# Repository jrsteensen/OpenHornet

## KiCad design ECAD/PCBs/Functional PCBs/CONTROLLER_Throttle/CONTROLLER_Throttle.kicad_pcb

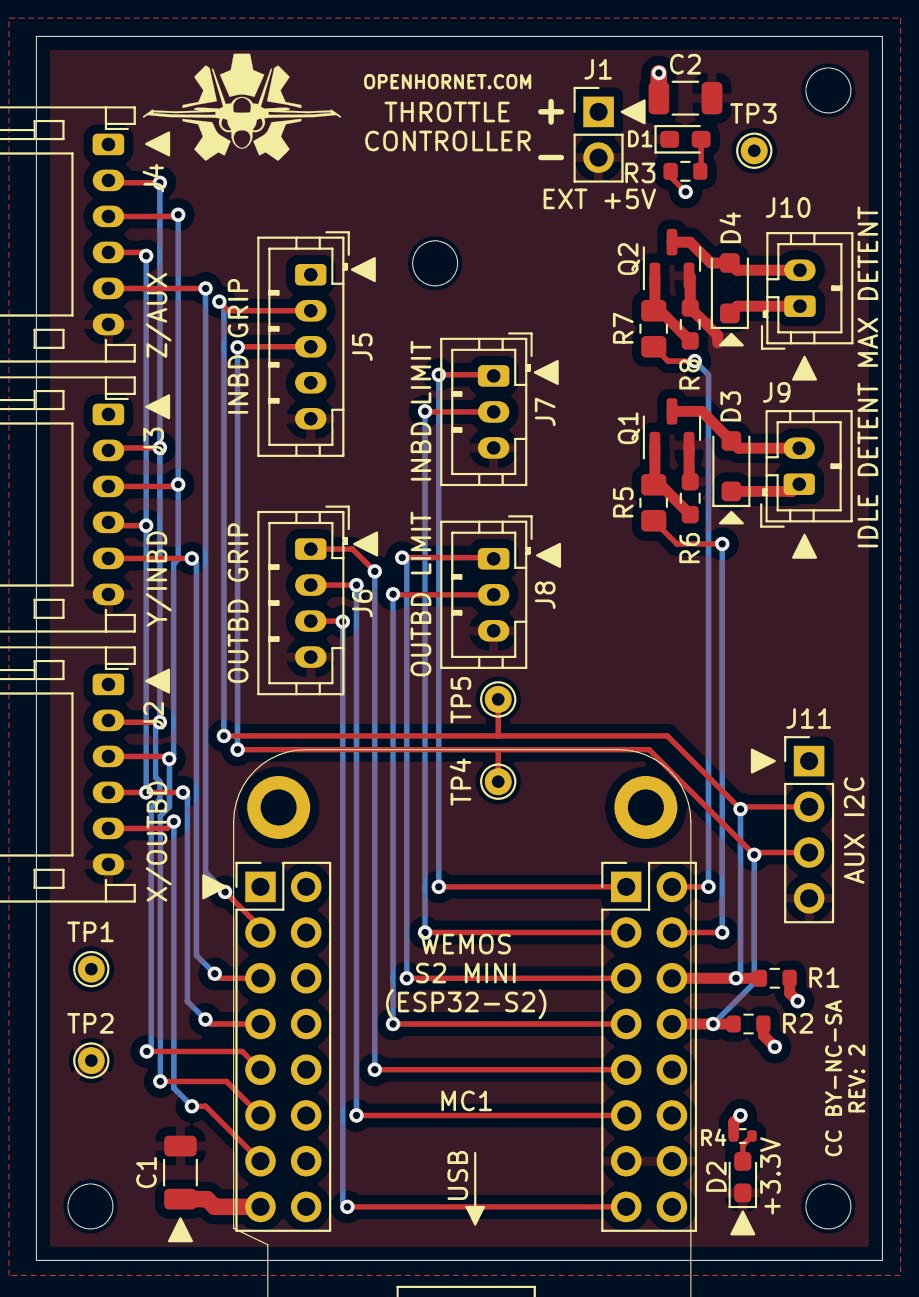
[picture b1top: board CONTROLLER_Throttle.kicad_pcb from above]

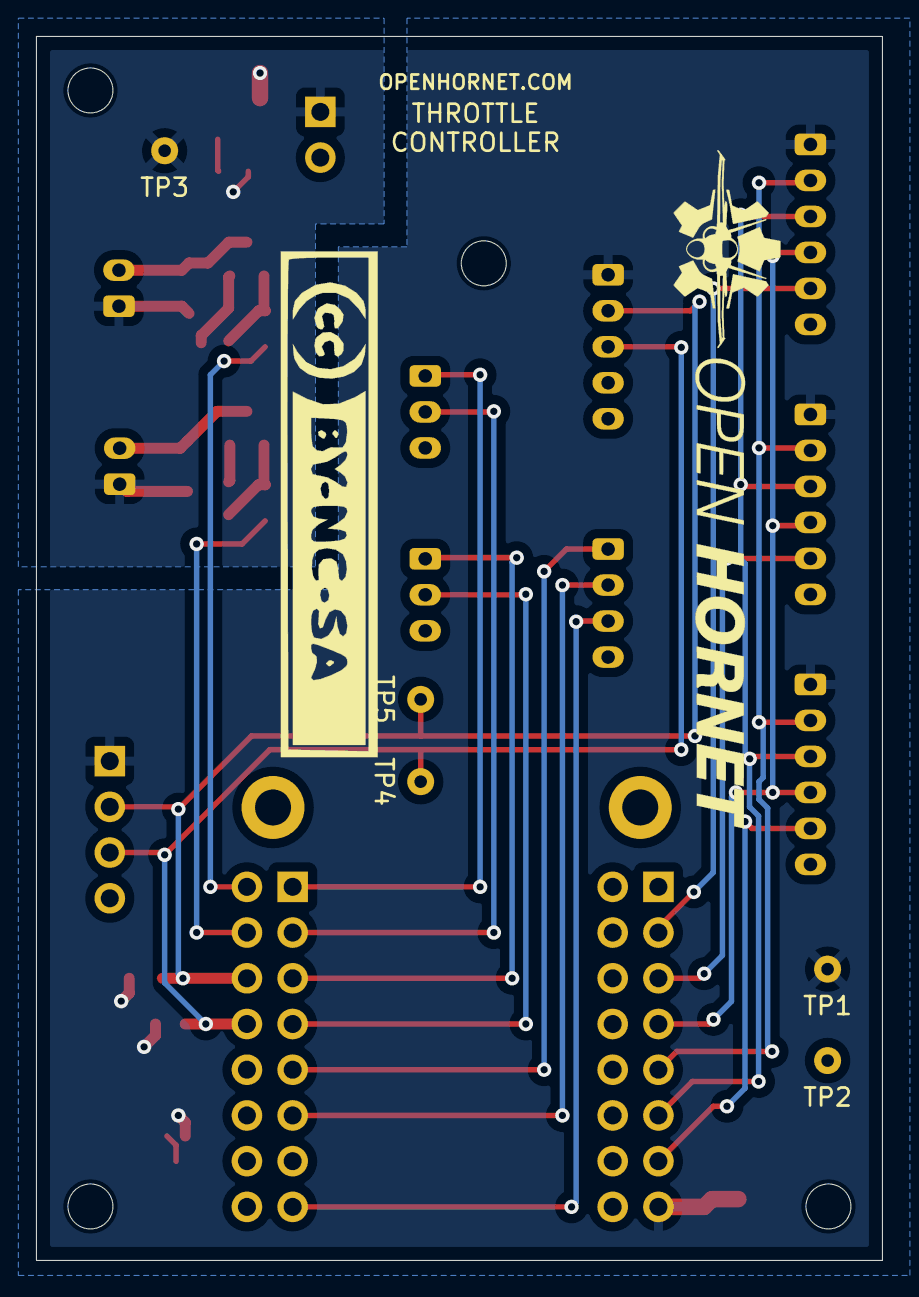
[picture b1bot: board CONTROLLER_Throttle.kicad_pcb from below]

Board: 2 copper layers, 47.0 x 68.0 mm, 40 parts (2 on the bottom side), 26 nets.

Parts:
C1, C2: 10uF; C_1206_3216Metric
D1: +5V_PWR; LED_0603_1608Metric_Pad1.05x0.95mm_HandSolder
D2: +3.3V_PWR; LED_0603_1608Metric_Pad1.05x0.95mm_HandSolder
D3, D4: 1N4002W; D_SOD-123F
J1: EXT +5V; PinHeader_1x02_P2.54mm_Vertical
J2: X/OUTBD; JST_PH_S6B-PH-K_1x06_P2.00mm_Horizontal
J3: Y/INBD; JST_PH_S6B-PH-K_1x06_P2.00mm_Horizontal
J4: Z/AUX; JST_PH_S6B-PH-K_1x06_P2.00mm_Horizontal
J5: INBD GRIP; JST_PH_B5B-PH-K_1x05_P2.00mm_Vertical
J6: OUTBD GRIP; JST_PH_B4B-PH-K_1x04_P2.00mm_Vertical
J7: INBD LIMIT; JST_PH_B3B-PH-K_1x03_P2.00mm_Vertical
J8: OUTBD LIMIT; JST_PH_B3B-PH-K_1x03_P2.00mm_Vertical
J9: IDLE DETENT; JST_PH_B2B-PH-K_1x02_P2.00mm_Vertical
J10: MAX DETENT; JST_PH_B2B-PH-K_1x02_P2.00mm_Vertical
J11: AUX I2C; PinHeader_1x04_P2.54mm_Vertical
LOGO1: OpenHornetLogoSmall; OH_LOGO_37.7mm_5.9mm
LOGO2: OpenHornetLogoSmall; CC-BY-NC-SA-Small
LOGO3: OpenHornetLogoSmall; OH_LOGO_ONLY_11x6mm
MC1: S2_MINI
MH1, MH2, MH3, MH4: MH; MountingHole_2.5mm
Q1, Q2: IRLML6402TRPBF; SOT-23
R1, R2: 4.7k; R_0603_1608Metric
R3: 120; R_0603_1608Metric
R4: 33; R_0402_1005Metric
R5, R7: 1K; R_0805_2012Metric_Pad1.20x1.40mm_HandSolder
R6, R8: 10K; R_0603_1608Metric_Pad0.98x0.95mm_HandSolder
TP1: 3v3; TestPoint_THTPad_D1.5mm_Drill0.7mm
TP2: GND; TestPoint_THTPad_D1.5mm_Drill0.7mm
TP3: 5VA; TestPoint_THTPad_D1.5mm_Drill0.7mm
TP4: SDA; TestPoint_THTPad_D1.5mm_Drill0.7mm
TP5: SCL; TestPoint_THTPad_D1.5mm_Drill0.7mm

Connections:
+3.3V: C1.1, J2.1, J3.1, J4.1, J5.1, J11.1, MC1.8 (+3.3V), R1.1, R2.2, R4.1, TP1.1
+5VA: C2.1, D3.1 (K), D4.1 (K), J1.1, J9.1, J10.1, R3.1, TP3.1
ATC ENGAGE: J6.3, MC1.24 (IO15)
CSx: J2.5, MC1.7 (IO12)
CSy: J3.5, MC1.3 (IO5)
CSz: J4.5, MC1.2 (IO3)
EXT LTS: J6.1, MC1.21 (IO21)
GND: C1.2, C2.2, D1.1 (K), D2.1 (K), J1.2, J2.6, J3.6, J4.6, J5.5, J6.4, J7.3, J8.3, J11.4, MC1.23 (GND1), MC1.31 (GND2), Q1.2 (S), Q2.2 (S), R6.2, R8.2, TP2.1
IDLE SOL SIG: MC1.26 (IO37), R5.1
INBD IDLE LIMIT: J7.2, MC1.18 (IO38)
INBD MAX LIMIT: J7.1, MC1.17 (IO40)
MAX SOL SIG: MC1.25 (IO39), R7.1
MISO: J2.2, J3.2, J4.2, MC1.5 (IO9/MISO)
MOSI: J2.3, J3.3, J4.3, MC1.6 (IO11/MOSI)
unnamed: D1.2 (A), R3.2
unnamed: D2.2 (A), R4.2
unnamed: D3.2 (A), J9.2, Q1.3 (D)
unnamed: D4.2 (A), J10.2, Q2.3 (D)
unnamed: Q1.1 (G), R5.2, R6.1
unnamed: Q2.1 (G), R7.2, R8.1
OUTBD IDLE LIMIT: J8.2, MC1.20 (IO34)
OUTBD MAX LIMIT: J8.1, MC1.19 (IO36)
RAID/FLIR: J6.2, MC1.22 (IO17/DAC1)
SCK: J2.4, J3.4, J4.4, MC1.4 (IO7/SCK)
SCL: J5.2, J11.2, MC1.27 (IO35/SCL), R1.2, TP5.1
SDA: J5.3, J11.3, MC1.28 (IO33/SDA), R2.1, TP4.1

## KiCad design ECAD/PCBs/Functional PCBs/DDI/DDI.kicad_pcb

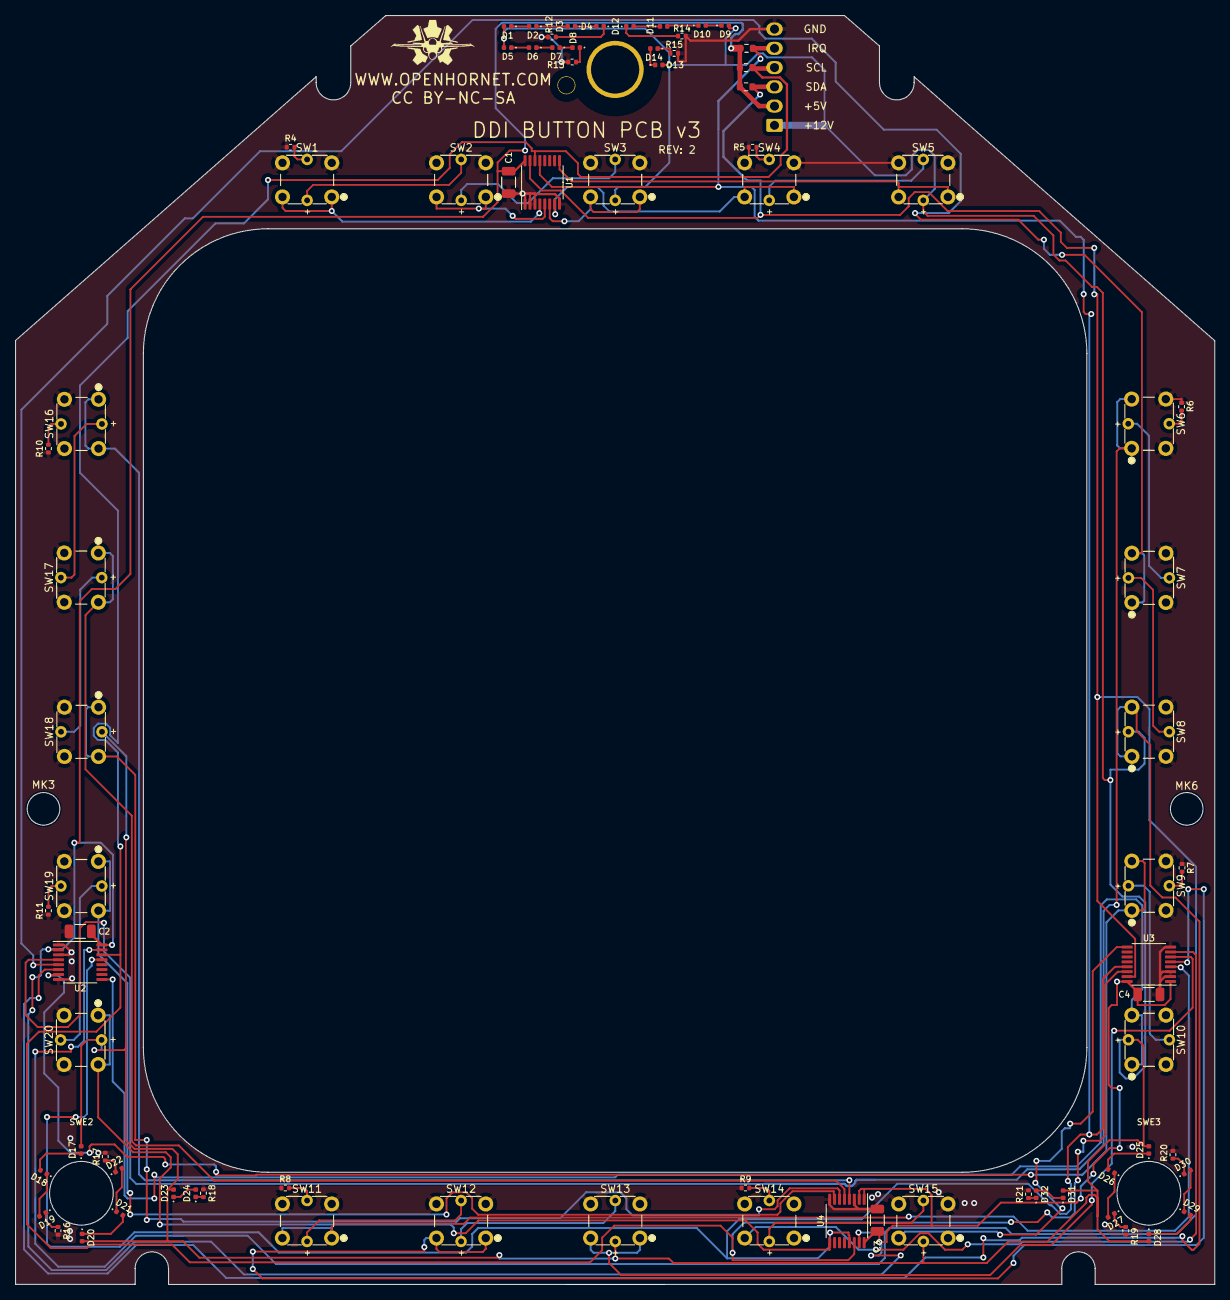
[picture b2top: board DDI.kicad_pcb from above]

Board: 2 copper layers, 158.2 x 167.4 mm, 85 parts (1 on the bottom side), 56 nets.

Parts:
C1, C2, C3, C4: 47uF; C_1206_3216Metric
D1, D2, D3, D4, D5, D6, D7, D8, D9, D10, D11, D12, D13, D14, D17, D18, D19, D20, D21, D22, D23, D24, D25, D26, D27, D28, D29, D30, D31, D32: LED; LED_0402_1005Metric
J1: Conn_01x06; Molex_KK-254_AE-6410-06A_1x06_P2.54mm_Vertical
MK3, MK6: MH; MountingHole_4.3mm_M4
R1, R2, R3: 10K; R_0603_1608Metric
R4, R6, R8, R10, R16, R17, R19, R20: 150; R_0402_1005Metric
R5, R7, R9, R11, R15, R18, R21: 270; R_0402_1005Metric
R12, R13, R14: 33; R_0402_1005Metric
SW1, SW2, SW3, SW4, SW5, SW6, SW7, SW8, SW9, SW10, SW11, SW12, SW13, SW14, SW15, SW16, SW17, SW18, SW19, SW20: TL1240GQ
SWE1: MRY106_RotarySW
SWE2, SWE3: MountingHole_8.4mm_M8
U1, U2, U3, U4: TCA9554PWR; TSSOP-16_4.4x5mm_P0.65mm

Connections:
+5V: C1.1, C2.1, C3.1, C4.1, J1.2, R1.1, R2.1, R3.1, U1.16, U2.2, U2.16, U3.1, U3.16, U4.1, U4.2, U4.16
/U1P0: SW1.1, U1.4
/U1P1: SW2.1, U1.5
/U1P2: SW3.1, U1.6
/U1P3: SW4.1, U1.7
/U1P4: SW5.1, U1.9
/U2P0: SW6.1, U2.4
/U2P1: SW7.1, U2.5
/U2P2: SW8.1, U2.6
/U2P3: SW9.1, U2.7
/U2P4: SW10.1, U2.9
/U3P0: SW11.1, U3.4
/U3P1: SW12.1, U3.5
/U3P2: SW13.1, U3.6
/U3P3: SW14.1, U3.7
/U3P4: SW15.1, U3.9
/U4P0: SW16.1, U4.4
/U4P1: SW17.1, U4.5
/U4P2: SW18.1, U4.6
/U4P3: SW19.1, U4.7
/U4P4: SW20.1, U4.9
GND: C1.2, C2.2, C3.2, C4.2, J1.6, R4.1, R5.1, R6.1, R7.1, R8.1, R9.1, R10.1, R11.1, R12.2, R13.2, R14.2, R15.2, R16.2, R17.2, R18.2, R19.2, R20.2, R21.2, SW1.2, SW2.2, SW3.2, SW4.2, SW5.2, SW6.2, SW7.2, SW8.2, SW9.2, SW10.2, SW11.2, SW12.2, SW13.2, SW14.2, SW15.2, SW16.2, SW17.2, SW18.2, SW19.2, SW20.2, U1.1, U1.2, U1.3, U1.8, U2.1, U2.3, U2.8, U3.2, U3.3, U3.8, U4.3, U4.8
IRQ: J1.5, R1.2, U1.13, U2.13, U3.13, U4.13
unnamed: D1.1, D2.2
unnamed: D2.1, D3.2
unnamed: D3.1, D4.2
unnamed: D4.1, R12.1
unnamed: D5.1, D6.2
unnamed: D6.1, D7.2
unnamed: D7.1, D8.2
unnamed: D8.1, R13.1
unnamed: D10.1, D11.2
unnamed: D9.1, D10.2
unnamed: D11.1, D12.2
unnamed: D12.1, R14.1
unnamed: D13.1, D14.2
unnamed: D14.1, R15.1
unnamed: D17.1, D18.2
unnamed: D18.1, D19.2
unnamed: D19.1, R16.1
unnamed: D20.1, D21.2
unnamed: D21.1, D22.2
unnamed: D22.1, R17.1
unnamed: D23.1, D24.2
unnamed: D24.1, R18.1
unnamed: D25.1, D26.2
unnamed: D26.1, D27.2
unnamed: D27.1, R19.1
unnamed: D28.1, D29.2
unnamed: D29.1, D30.2
unnamed: D30.1, R20.1
unnamed: D31.1, D32.2
unnamed: D32.1, R21.1
SCL: J1.4, R2.2, U1.14, U2.14, U3.14, U4.14
SDA: J1.3, R3.2, U1.15, U2.15, U3.15, U4.15
VCC: D1.2, D5.2, D9.2, D13.2, D17.2, D20.2, D23.2, D25.2, D28.2, D31.2, J1.1

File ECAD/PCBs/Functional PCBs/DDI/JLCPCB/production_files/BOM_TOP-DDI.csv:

Comment,Designator,Footprint,LCSC
LED,"D1,D10,D11,D12,D13,D14,D17,D18,D19,D2,D20,D21,D22,D23,D24,D25,D26,D27,D28,D29,D3,D30,D31,D32,D4,D5,D6,D7,D8,D9",LED_0402_1005Metric,C130723
150,"R10,R16,R17,R19,R20,R4,R6,R8",R_0402_1005Metric,C25082
270,"R11,R15,R18,R21,R5,R7,R9",R_0402_1005Metric,C25099
33,"R12,R13,R14",R_0402_1005Metric,C25105
10K,"R1,R2,R3",R_0603_1608Metric,C25804
TCA9554PWR,"U1,U2,U3,U4",TSSOP-16_4.4x5mm_P0.65mm,C477924
47uF,"C1,C2,C3,C4",C_1206_3216Metric,C96123
TL1240GQ_old,SW1,TL1240GQ_old,
TL1240GQ_old,SW2,TL1240GQ_old,
TL1240GQ_old,SW3,TL1240GQ_old,
TL1240GQ_old,SW4,TL1240GQ_old,
TL1240GQ_old,SW5,TL1240GQ_old,
TL1240GQ_old,SW6,TL1240GQ_old,
TL1240GQ_old,SW7,TL1240GQ_old,
TL1240GQ_old,SW8,TL1240GQ_old,
TL1240GQ_old,SW9,TL1240GQ_old,
TL1240GQ_old,SW10,TL1240GQ_old,
TL1240GQ_old,SW11,TL1240GQ_old,
TL1240GQ_old,SW12,TL1240GQ_old,
TL1240GQ_old,SW13,TL1240GQ_old,
TL1240GQ_old,SW14,TL1240GQ_old,
TL1240GQ_old,SW15,TL1240GQ_old,
TL1240GQ_old,SW16,TL1240GQ_old,
TL1240GQ_old,SW17,TL1240GQ_old,
TL1240GQ_old,SW18,TL1240GQ_old,
TL1240GQ_old,SW19,TL1240GQ_old,
TL1240GQ_old,SW20,TL1240GQ_old,

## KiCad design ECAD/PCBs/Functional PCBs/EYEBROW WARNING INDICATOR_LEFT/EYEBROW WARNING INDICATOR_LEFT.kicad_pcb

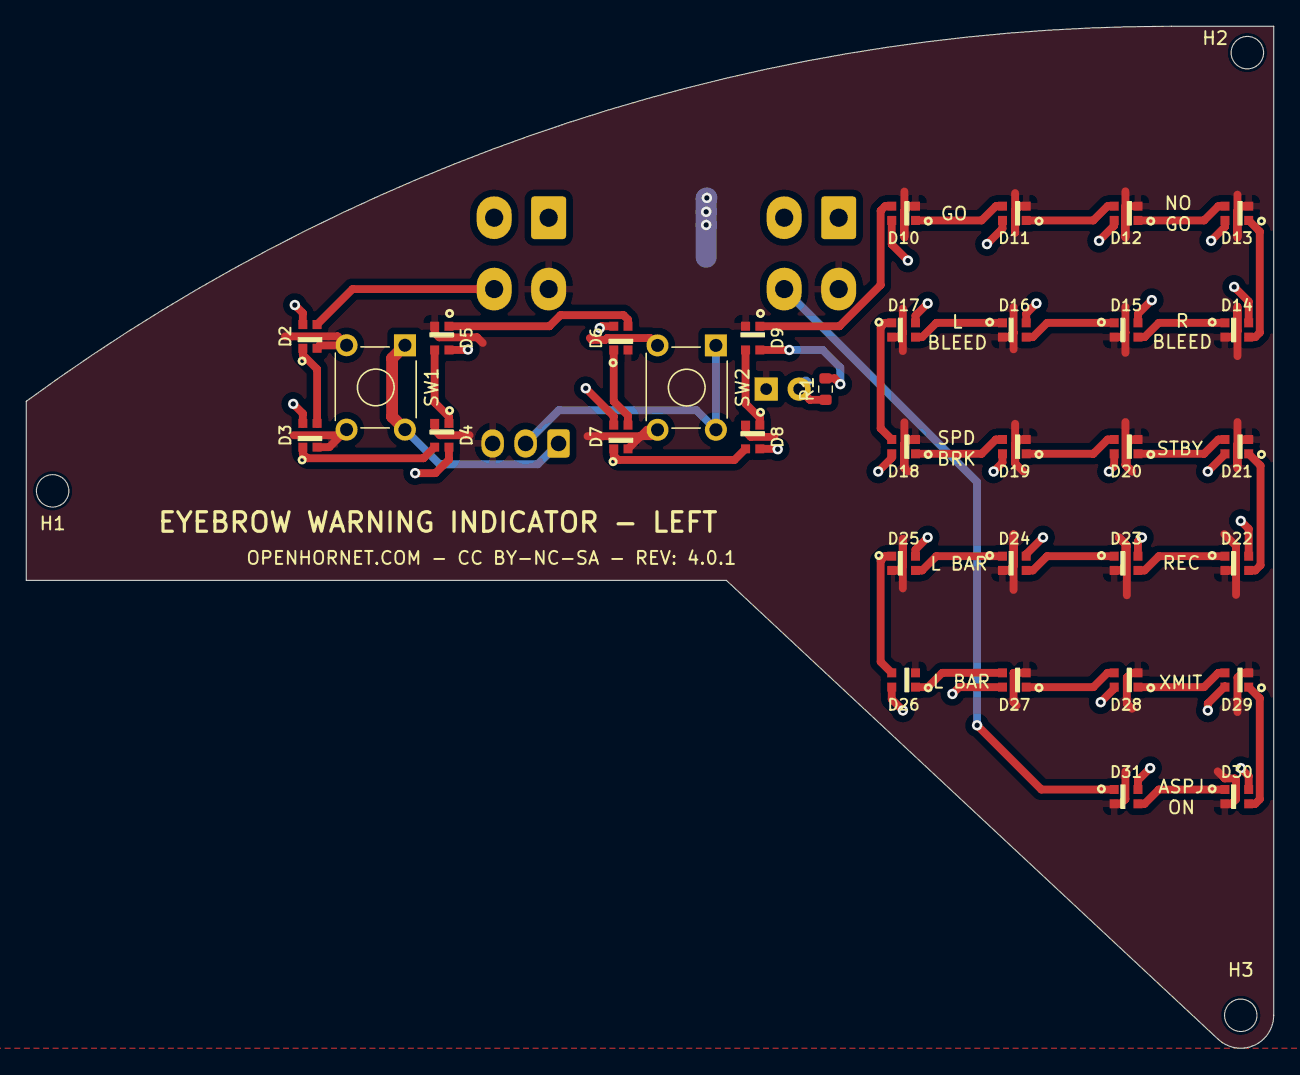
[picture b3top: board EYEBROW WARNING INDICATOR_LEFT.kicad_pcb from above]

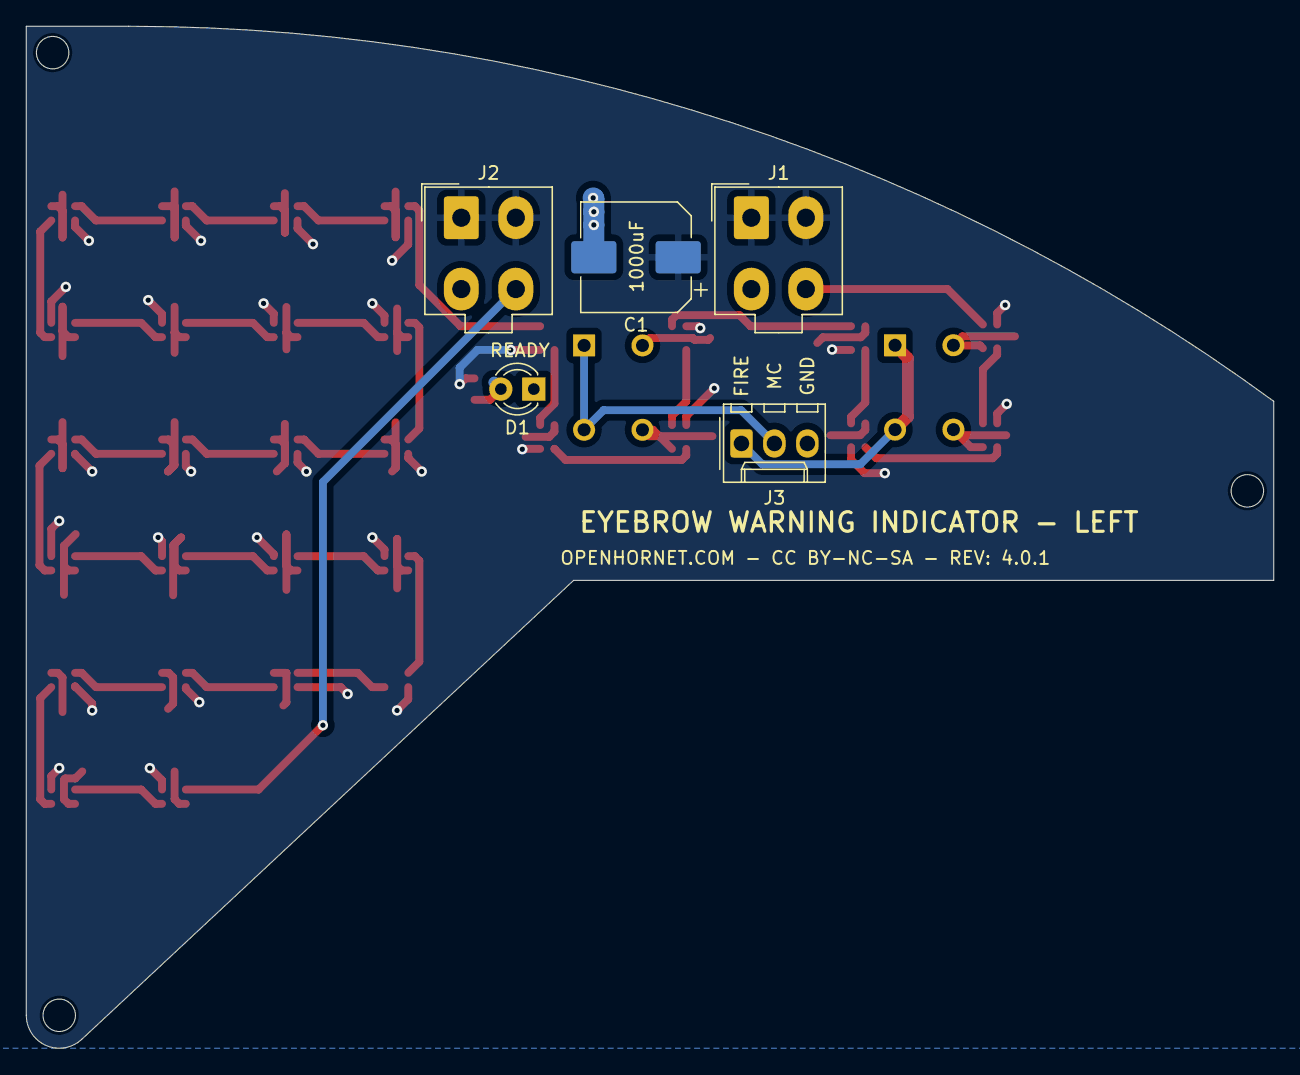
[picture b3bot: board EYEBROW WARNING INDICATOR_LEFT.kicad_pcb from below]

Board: 2 copper layers, 96.1 x 78.8 mm, 41 parts (5 on the bottom side), 36 nets.

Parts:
C1: 1000 nF; CP_Elec_8x10
D1: PWR; LED_D3.0mm
D2, D3, D4, D5, D6, D7, D8, D9, D10, D11, D12, D13, D14, D15, D16, D17, D18, D19, D20, D21, D22, D23, D24, D25, D26, D27, D28, D29, D30, D31: LED; WS2812-2020
H1, H2, H3: MountingHole; MountingHole_2.5mm
J1: BL IN; Molex_Mini-Fit_Jr_5566-04A_2x02_P4.20mm_Vertical
J2: BL OUT; Molex_Mini-Fit_Jr_5566-04A_2x02_P4.20mm_Vertical
J3: SW; Molex_KK-254_AE-6410-03A_1x03_P2.54mm_Vertical
R1: 120; R_0603_1608Metric
SW1: FIRE; SW_TH_Tactile_Omron_B3F-10xx
SW2: MC/APU FIRE; SW_TH_Tactile_Omron_B3F-10xx

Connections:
+5V: C1.1, D2.4, D3.4, D4.4, D5.4, D6.4, D7.4, D8.4, D9.4, D10.4, D11.4, D12.4, D13.4, D14.4, D15.4, D16.4, D17.4, D18.4, D19.4, D20.4, D21.4, D22.4, D23.4, D24.4, D25.4, D26.4, D27.4, D28.4, D29.4, D30.4, D31.4, J1.1, J1.2, J2.1, J2.2, R1.2
/DIN: D2.3, J1.4
/DOUT: D31.1, J2.4
/DOUT1: D9.1, D10.3
/DOUT2: D17.1, D18.3
/DOUT3: D25.1, D26.3
/FIRE_SW: J3.1, SW1.1, SW1.2
/MC_SW: J3.2, SW2.1, SW2.2
GND: C1.2, D1.1 (K), D2.2, D3.2, D4.2, D5.2, D6.2, D7.2, D8.2, D9.2, D10.2, D11.2, D12.2, D13.2, D14.2, D15.2, D16.2, D17.2, D18.2, D19.2, D20.2, D21.2, D22.2, D23.2, D24.2, D25.2, D26.2, D27.2, D28.2, D29.2, D30.2, D31.2, J1.3, J2.3, J3.3
unnamed: D1.2 (A), R1.1
unnamed: D2.1, D3.3
unnamed: D3.1, D4.3
unnamed: D4.1, D5.3
unnamed: D5.1, D6.3
unnamed: D6.1, D7.3
unnamed: D7.1, D8.3
unnamed: D8.1, D9.3
unnamed: D10.1, D11.3
unnamed: D11.1, D12.3
unnamed: D12.1, D13.3
unnamed: D13.1, D14.3
unnamed: D14.1, D15.3
unnamed: D15.1, D16.3
unnamed: D16.1, D17.3
unnamed: D18.1, D19.3
unnamed: D19.1, D20.3
unnamed: D20.1, D21.3
unnamed: D21.1, D22.3
unnamed: D22.1, D23.3
unnamed: D23.1, D24.3
unnamed: D24.1, D25.3
unnamed: D26.1, D27.3
unnamed: D27.1, D28.3
unnamed: D28.1, D29.3
unnamed: D29.1, D30.3
unnamed: D30.1, D31.3

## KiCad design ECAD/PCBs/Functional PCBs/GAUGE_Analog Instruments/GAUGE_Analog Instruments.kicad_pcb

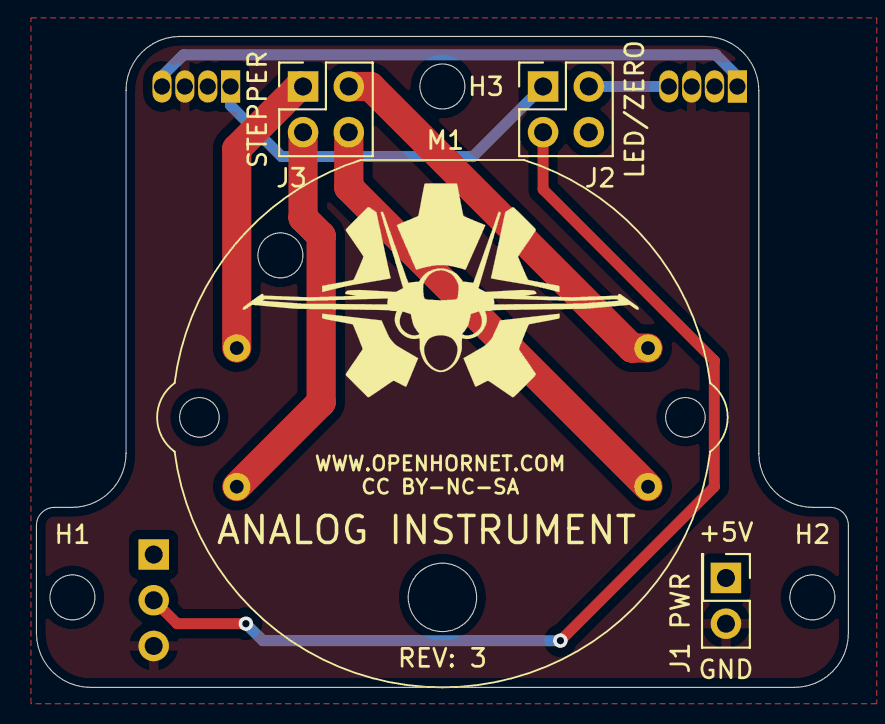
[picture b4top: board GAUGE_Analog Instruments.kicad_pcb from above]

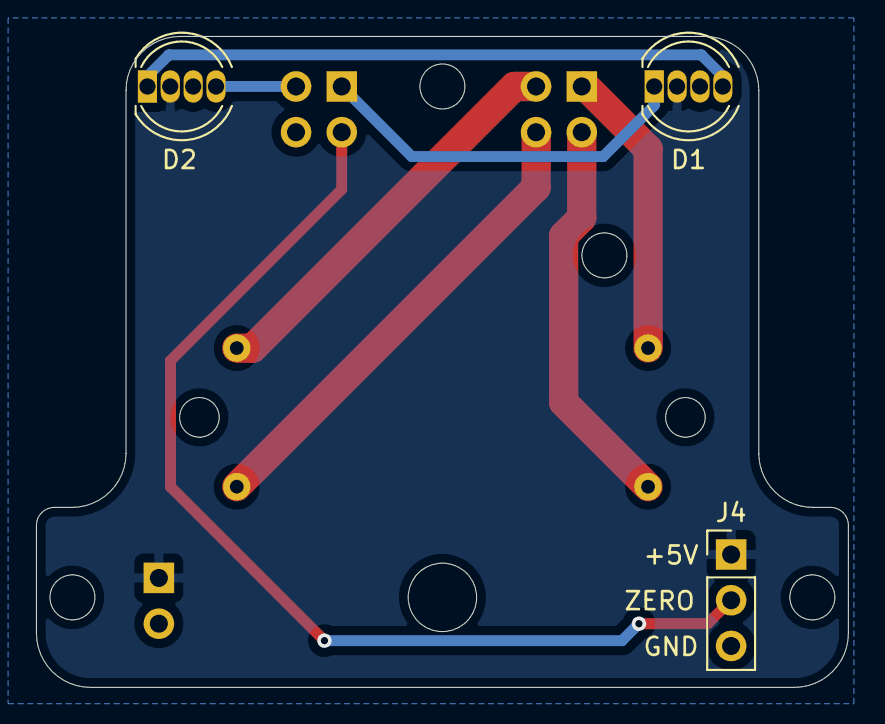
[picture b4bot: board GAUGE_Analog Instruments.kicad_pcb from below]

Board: 2 copper layers, 45.1 x 36.2 mm, 10 parts (3 on the bottom side), 10 nets.

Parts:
D1, D2: 1938; LED_D5.0mm-4_RGB
H1, H2, H3: MountingHole; MountingHole_2.5mm
J1: PWR; PinHeader_2x01_P2.54mm_Vertical
J2: LED/ZERO; PinHeader_2x02_P2.54mm_Vertical
J3: STEPPER; PinHeader_2x02_P2.54mm_Vertical
J4: ZERO; PinHeader_1x03_P2.54mm_Vertical
M1: VID29-02

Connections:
+5V: D1.2, D2.2, J1.1, J4.1
/COIL1: J3.1, M1.1
/COIL2: J3.3, M1.2
/COIL3: J3.4, M1.3
/COIL4: J3.2, M1.4
/LED_DIN: D1.1, J2.1
/LED_DOUT: D2.4, J2.2
/ZERO_DETECT: J2.3, J4.2
GND: D1.3, D2.3, J1.2, J4.3
unnamed: D1.4, D2.1

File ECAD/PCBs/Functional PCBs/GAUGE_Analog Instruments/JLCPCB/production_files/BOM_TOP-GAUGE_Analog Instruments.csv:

Comment,Designator,Footprint,LCSC
STEPPER,J3,PinHeader_2x02_P2.54mm_Vertical,
LED/ZERO,J2,PinHeader_2x02_P2.54mm_Vertical,
PWR,J1,PinHeader_2x01_P2.54mm_Vertical,
VID29-02,M1,VID29-02,

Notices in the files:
ECAD/PCBs/Functional PCBs/EYEBROW WARNING INDICATOR_LEFT/EYEBROW WARNING INDICATOR_LEFT.kicad_pcb:
OPENHORNET.COM - CC BY-NC-SA - REV: 4.0.1
